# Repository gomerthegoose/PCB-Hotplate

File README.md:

# PCB-Hotplate

- pcb based hot plate with swapable heater -

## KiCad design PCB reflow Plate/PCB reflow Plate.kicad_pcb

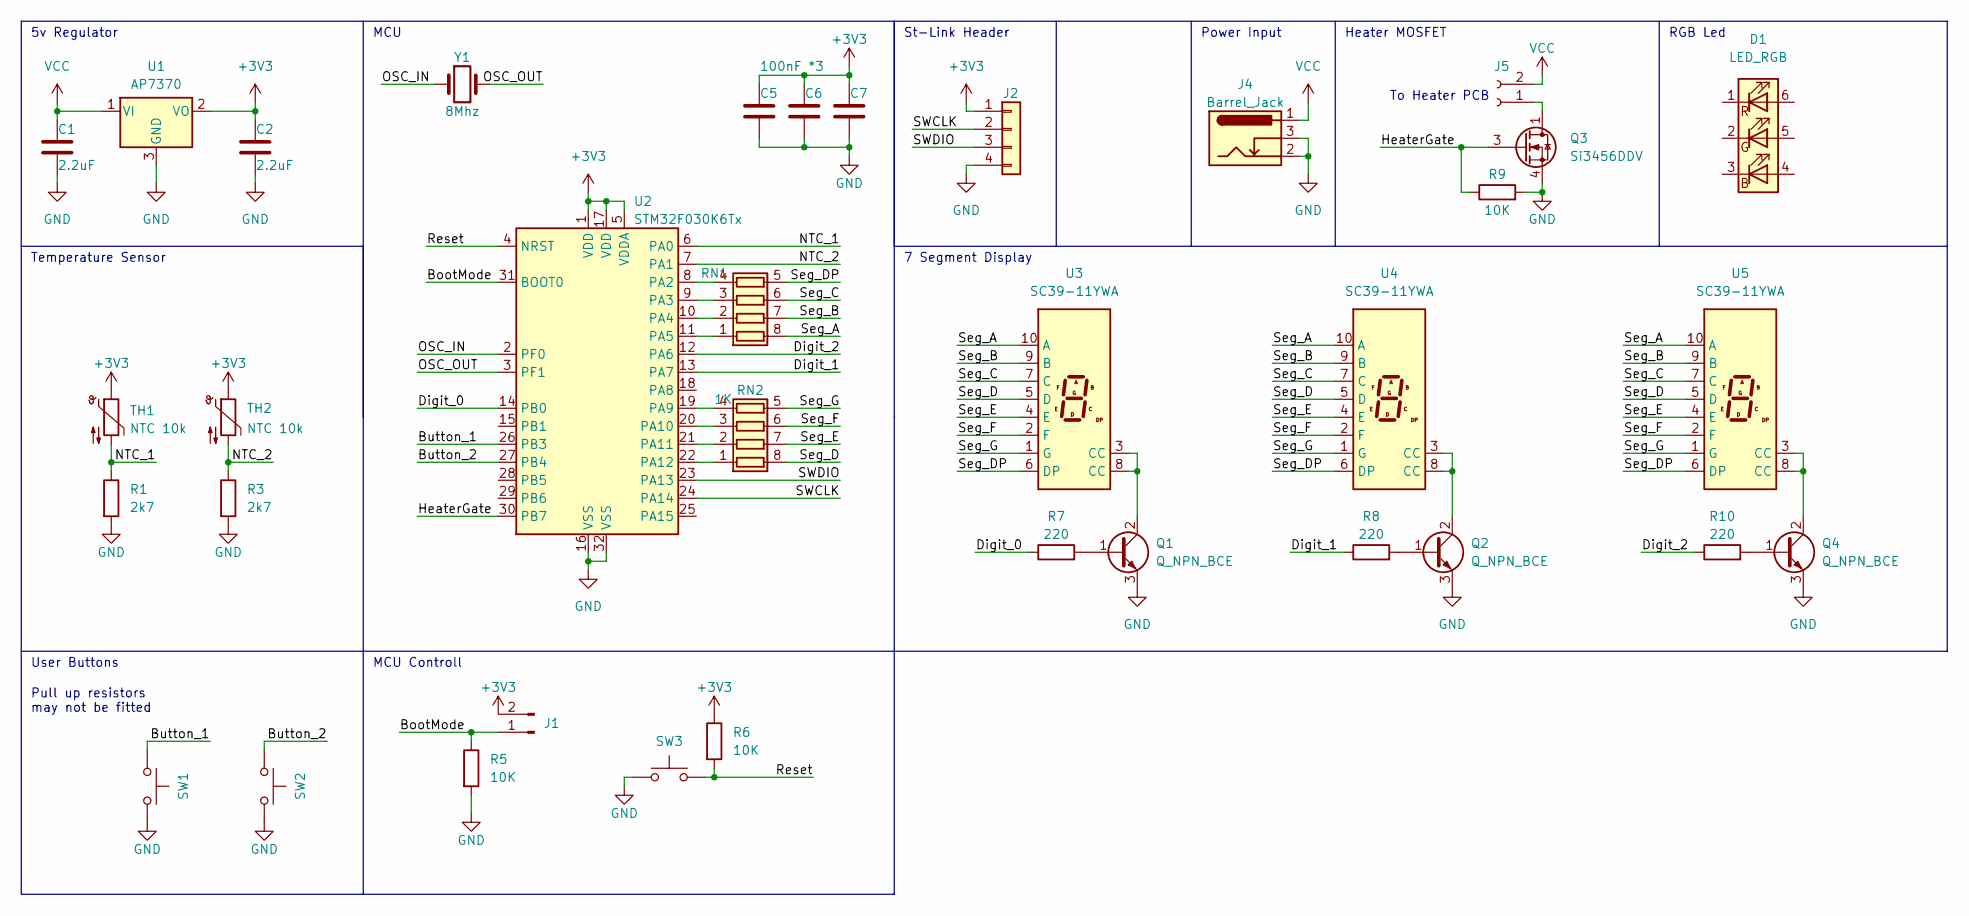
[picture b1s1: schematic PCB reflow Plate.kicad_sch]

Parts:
C1, C2: 2.2uF; C_0603_1608Metric_Pad1.08x0.95mm_HandSolder
C5: 100nF *3; C_0603_1608Metric_Pad1.08x0.95mm_HandSolder
C6, C7: 100nF; C_0603_1608Metric_Pad1.08x0.95mm_HandSolder
D1: LED_RGB
J1: Conn_01x02_Male; PinHeader_1x02_P2.54mm_Vertical
J2: Conn_01x04; PinHeader_1x04_P2.54mm_Vertical
J4: Barrel_Jack; BarrelJack_Wuerth_6941xx301002
J5: Conn_01x02_Female; PinHeader_1x02_P2.54mm_Horizontal
Q1, Q2, Q4: Q_NPN_BCE; SOT-23
Q3: Si3456DDV; TSOP-6_1.65x3.05mm_P0.95mm
R1, R3: 2k7; R_0603_1608Metric_Pad0.98x0.95mm_HandSolder
R5, R6, R9: 10K; R_0603_1608Metric_Pad0.98x0.95mm_HandSolder
R7, R8, R10: 220; R_0603_1608Metric_Pad0.98x0.95mm_HandSolder
RN1, RN2: 1K; R_Array_Convex_4x0603
SW1, SW2: SW_Push; SW_SPST_TL3342
SW3: SW_Push; SW_SPST_CK_RS282G05A3
TH1, TH2: NTC 10k; PinHeader_1x02_P1.27mm_Vertical
U1: AP7370; SOT-23
U2: STM32F030K6Tx; LQFP-32_7x7mm_P0.8mm
U3, U4, U5: SC39-11YWA; 7SegmentLED_LTS6760_LTS6780
Y1: 8Mhz; Crystal_SMD_HC49-SD_HandSoldering

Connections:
+3V3: C2.1, C5.1, C6.1, C7.1, J1.2, J2.1, R6.1, TH1.1, TH2.1, U1.2 (VO), U2.1 (VDD), U2.5 (VDDA), U2.17 (VDD)
/BootMode: J1.1, R5.1, U2.31 (BOOT0)
/Button_1: SW1.1, U2.26 (PB3)
/Button_2: SW2.1, U2.27 (PB4)
/Digit_0: R7.1, U2.14 (PB0)
/Digit_1: R8.1, U2.13 (PA7)
/Digit_2: R10.1, U2.12 (PA6)
/HeaterGate: Q3.3 (G), R9.1, U2.30 (PB7)
/NTC_1: R1.1, TH1.2, U2.6 (PA0)
/NTC_2: R3.1, TH2.2, U2.7 (PA1)
/OSC_IN: U2.2 (PF0), Y1.1
/OSC_OUT: U2.3 (PF1), Y1.2
/Reset: R6.2, SW3.2, U2.4 (NRST)
/SWCLK: J2.2, U2.24 (PA14)
/SWDIO: J2.3, U2.23 (PA13)
/Seg_A: RN1.8 (R1.2), U3.10 (A), U4.10 (A), U5.10 (A)
/Seg_B: RN1.7 (R2.2), U3.9 (B), U4.9 (B), U5.9 (B)
/Seg_C: RN1.6 (R3.2), U3.7 (C), U4.7 (C), U5.7 (C)
/Seg_D: RN2.8 (R1.2), U3.5 (D), U4.5 (D), U5.5 (D)
/Seg_DP: RN1.5 (R4.2), U3.6 (DP), U4.6 (DP), U5.6 (DP)
/Seg_E: RN2.7 (R2.2), U3.4 (E), U4.4 (E), U5.4 (E)
/Seg_F: RN2.6 (R3.2), U3.2 (F), U4.2 (F), U5.2 (F)
/Seg_G: RN2.5 (R4.2), U3.1 (G), U4.1 (G), U5.1 (G)
GND: C1.2, C2.2, C5.2, C6.2, C7.2, J2.4, J4.2, J4.3, Q1.3 (E), Q2.3 (E), Q3.4 (S), Q4.3 (E), R1.2, R3.2, R5.2, R9.2, SW1.2, SW2.2, SW3.1, U1.3 (GND), U2.16 (VSS), U2.32 (VSS)
unnamed: Q1.1 (B), R7.2
unnamed: Q1.2 (C), U3.3 (CC), U3.8 (CC)
unnamed: Q2.1 (B), R8.2
unnamed: Q2.2 (C), U4.3 (CC), U4.8 (CC)
unnamed: J5.1, Q3.1 (D), Q3.2 (D), Q3.5 (D), Q3.6 (D)
unnamed: Q4.1 (B), R10.2
unnamed: Q4.2 (C), U5.3 (CC), U5.8 (CC)
unnamed: RN2.1 (R1.1), U2.22 (PA12)
unnamed: RN2.2 (R2.1), U2.21 (PA11)
unnamed: RN2.3 (R3.1), U2.20 (PA10)
unnamed: RN2.4 (R4.1), U2.19 (PA9)
unnamed: RN1.4 (R4.1), U2.8 (PA2)
unnamed: RN1.3 (R3.1), U2.9 (PA3)
unnamed: RN1.2 (R2.1), U2.10 (PA4)
unnamed: RN1.1 (R1.1), U2.11 (PA5)
VCC: C1.1, J4.1, J5.2, U1.1 (VI)

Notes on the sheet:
St-Link Header
MCU
MCU Controll
To Heater PCB
Pull up resistors may not be fitted
Heater MOSFET
Temperature Sensor
Power Input
User Buttons
5v Regulator
RGB Led
7 Segment Display

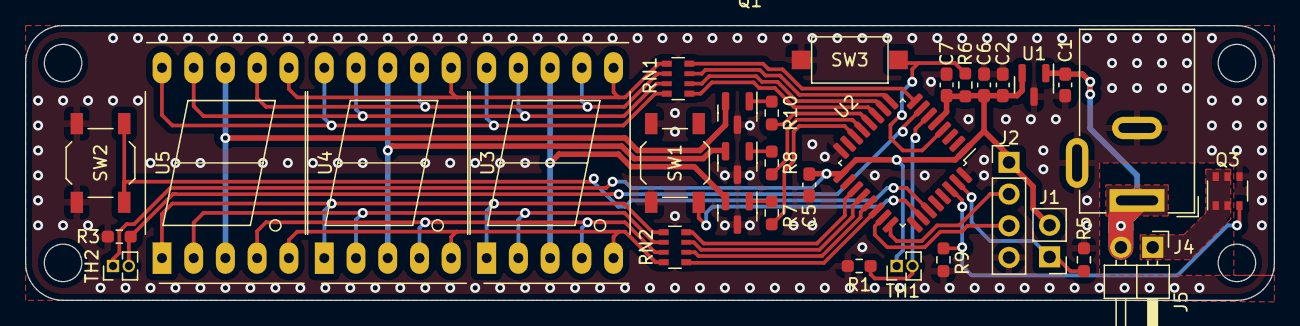
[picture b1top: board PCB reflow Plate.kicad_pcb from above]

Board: 2 copper layers, 100.0 x 22.0 mm, 33 parts (0 on the bottom side), 38 nets.

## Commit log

2023-01-26 mcu and mosfet
2023-01-27 7 segment display, NTC, heater mosfet, new MCU
2023-01-28 initial pcb design
2023-01-29 rev 1 final design
